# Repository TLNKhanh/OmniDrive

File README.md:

# OmniDrive

Dual H-bridge motor driver + ESP32 + USB-C PD, squeezed into a 45×59.5mm 2-layer board.

I wanted a board that could work with a single USB-C port and have it drive two motors (or 2 pairs if configured) while able to measure the board's current draw.

*Full schematic — click image or [open PDF](hardware/schematic.pdf)*

*PCB top copper layer — [open PDF](hardware/PCB_Top.pdf)*

*PCB bottom copper layer — [open PDF](hardware/PCB_Bottom.pdf)*

## What it does

- Drives 2 or 4 DC motors (configurable) with two DRV8833 H-bridges, one DRV8833 is optimal, up to 1.5A per channel.
- Negotiates power over USB-C via CH224K to get 9V from power supply
- Measures total motor current with an INA219 over I2C
- Lets you program the ESP32 over USB through the CH340C, with automatic boot/reset
- Breaks out power lines and 14 GPIOs + I2C on a header for sensors, encoders, whatever
- Configurable 2S / 1S battery pack via solder pads

## Why I built it

I wanted something that could serve for multiple RC car or stepper driving projects without having to combine separate modules.

## Specs

| Function| Component |
|------|------|
| MCU | ESP32-WROOM-32E |
| Motor drivers | 2× DRV8833 (HTSSOP-16 with thermal pad) |
| USB-C PD | CH224K sink, negotiates 9V |
| Current sense | INA219, 0.1Ω shunt, I2C |
| USB-UART | CH340C with auto DTR/RTS |
| Logic power | ME6211C50 (5V), ME6211C33 (3.3V) |
| Breakout | 12 GPIO through 2x 3x2 header, Power through 1x 3x1 header|
| PCB | 2-layer, 1.6mm FR4, 45×59.5mm |

## Power flow

USB-C VBUS → CH224K negotiates voltage → +BATT rail

+BATT splits three ways:
- Directly to the DRV8833 motor drivers
- Through a 5V LDO (ME6211C50) for the CH340C and other devices
- It also then goes through a 3.3V LDO (ME6211C33) for the ESP32, INA219, WS2812,...

Motor current goes through a shared 0.1Ω sense resistor before reaching the drivers, so the INA219 sees total bus current. Per-motor would need two INA219s (maybe for later).

## Known issues / things to fix

A few things I'll change next version:

- The ME6211C33 is rated for 500mA and ESP32 can spike past that during WiFi TX. On a long USB-C cable with some voltage drop, the battery rail might sag enough to make the 3.3V regulator drop out. An AP2112 or similar low-dropout part would be safer.

- Didn't add TVS diodes on the USB-C CC/D+/D- lines or the motor outputs

- As mentioned, only total motor current. Can't tell which motor is drawing what.

## Files in hardware/

```
hardware/
├── schematic.pdf          — full schematic (click to view)
├── PCB_Top.pdf            — top copper render
├── PCB_Bottom.pdf         — bottom copper render
├── gerbers.zip            — Gerbers + drill files
├── bom.csv                — BOM for JLCPCB assembly
├── pick-place.csv         — centroid file
├── kicad/                 — source KiCad project
└── photos/                — PNG renders of schematic + PCB
```

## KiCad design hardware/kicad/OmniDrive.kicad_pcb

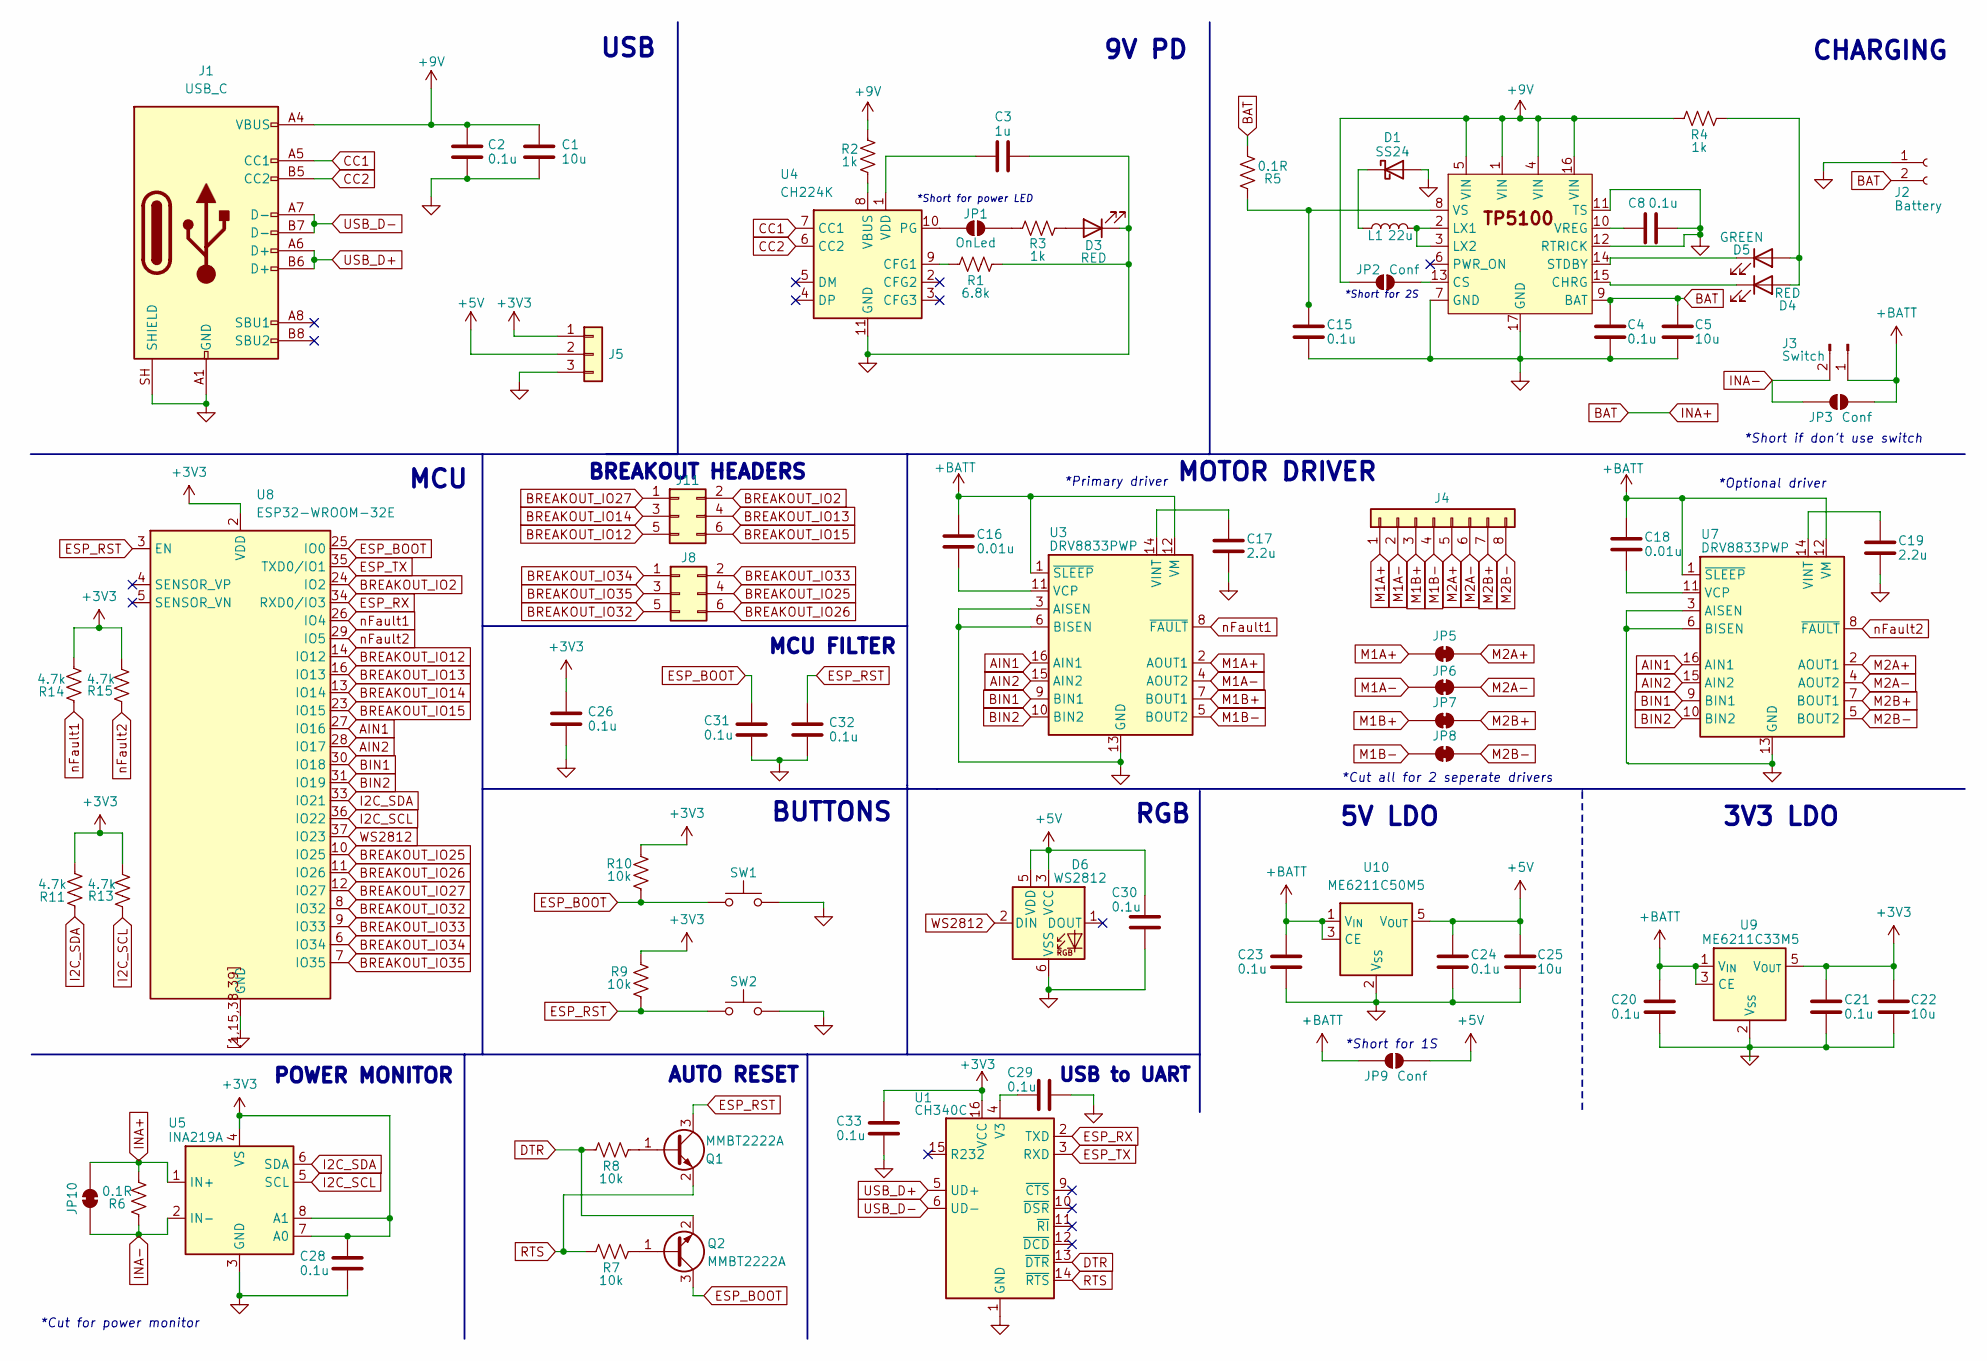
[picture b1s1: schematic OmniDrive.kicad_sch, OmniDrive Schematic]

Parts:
C1, C5, C22, C25: 10u; C_0603_1608Metric_Pad1.08x0.95mm_HandSolder
C2, C4, C8, C15, C20, C21, C23, C24, C26, C28, C29, C30, C31, C32, C33: 0.1u; C_0603_1608Metric_Pad1.08x0.95mm_HandSolder
C3: 1u; C_0603_1608Metric_Pad1.08x0.95mm_HandSolder
C16, C18: 0.01u; C_0603_1608Metric_Pad1.08x0.95mm_HandSolder
C17, C19: 2.2u; C_0603_1608Metric_Pad1.08x0.95mm_HandSolder
D1: SS24; D_SMA
D3, D4: RED; LED_0603_1608Metric_Pad1.05x0.95mm_HandSolder
D5: GREEN; LED_0603_1608Metric_Pad1.05x0.95mm_HandSolder
D6: WS2812; LED_WS2812_PLCC6_5.0x5.0mm_P1.6mm
J1: USB_C; USB_C_Receptacle_HCTL_HC-TYPE-C-16P-01A
J2: Battery; PinHeader_1x02_P2.54mm_Vertical
J3: Switch; PinHeader_1x02_P2.54mm_Vertical
J4: Conn_01x08; PinSocket_1x08_P2.54mm_Vertical
J5: Conn_01x03; PinSocket_1x03_P2.54mm_Vertical
J8, J11: Conn_02x03_Odd_Even; PinHeader_2x03_P2.54mm_Vertical
JP1: OnLed; SolderJumper-2_P1.3mm_Bridged_RoundedPad1.0x1.5mm
JP2, JP3, JP9: Conf; SolderJumper-2_P1.3mm_Open_TrianglePad1.0x1.5mm
JP5, JP6, JP7, JP8, JP10: BridgedJumper; SolderJumper-2_P1.3mm_Bridged_RoundedPad1.0x1.5mm
L1: 22u; L_Changjiang_FXL0630
Q1, Q2: MMBT2222A; SOT-23
R1: 6.8k; R_0603_1608Metric_Pad0.98x0.95mm_HandSolder
R2, R3, R4: 1k; R_0603_1608Metric_Pad0.98x0.95mm_HandSolder
R5, R6: 0.1R; R_2512_6332Metric_Pad1.40x3.35mm_HandSolder
R7, R8, R9, R10: 10k; R_0603_1608Metric_Pad0.98x0.95mm_HandSolder
R11, R13, R14, R15: 4.7k; R_0603_1608Metric_Pad0.98x0.95mm_HandSolder
SW1, SW2: SW_Push; SW_Push_1P1T_NO_E-Switch_TL3301NxxxxxG
U1: CH340C; SOIC-16_3.9x9.9mm_P1.27mm
U2: NXP_VQFN-16-1EP_4x4mm_P0.65mm_EP2.1x2.1mm
U3, U7: DRV8833PWP; HTSSOP-16-1EP_4.4x5mm_P0.65mm_EP3.4x5mm_Mask2.46x2.31mm_The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
U4: CH224K; SSOP-10-1EP_3.9x4.9mm_P1mm_EP2.1x3.3mm
U5: INA219A; SOT-23-8
U8: ESP32-WROOM-32E
U9: ME6211C33M5; SOT-23-5
U10: ME6211C50M5; SOT-23-5

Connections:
+3V3: C21.1, C22.1, C26.1, C28.1, C33.2, J5.1, R9.1, R10.1, R11.2, R13.2, R14.2, R15.2, U1.16 (VCC), U5.4 (VS), U5.7 (A0), U5.8 (A1), U8.2 (VDD), U9.5 (V_{OUT})
+5V: C24.1, C25.1, C30.1, D6.3 (VCC), D6.5 (VDD), J5.2, JP9.1 (A), U10.5 (V_{OUT})
+9V: C1.1, C2.1, J1.A4 (VBUS), J1.A9 (VBUS), J1.B4 (VBUS), J1.B9 (VBUS), JP2.2 (B), R2.2, R4.2, U2.1 (VIN), U2.4 (VIN), U2.5 (VIN), U2.16 (VIN)
+BATT: C16.1, C18.1, C20.1, C23.1, J3.1, JP3.1 (A), JP9.2 (B), U3.1 (~SLEEP), U3.12 (VM), U7.1 (~SLEEP), U7.12 (VM), U9.1 (V_{IN}), U9.3 (CE), U10.1 (V_{IN}), U10.3 (CE)
AIN1: U3.16 (AIN1), U7.16 (AIN1), U8.27 (IO16)
AIN2: U3.15 (AIN2), U7.15 (AIN2), U8.28 (IO17)
BAT: C4.1, C5.1, J2.2, JP10.2 (B), R5.1, R6.1, U2.9 (BAT), U5.1 (IN+)
BIN1: U3.9 (BIN1), U7.9 (BIN1), U8.30 (IO18)
BIN2: U3.10 (BIN2), U7.10 (BIN2), U8.31 (IO19)
BREAKOUT_IO2: J11.2, U8.24 (IO2)
BREAKOUT_IO12: J11.5, U8.14 (IO12)
BREAKOUT_IO13: J11.4, U8.16 (IO13)
BREAKOUT_IO14: J11.3, U8.13 (IO14)
BREAKOUT_IO15: J11.6, U8.23 (IO15)
BREAKOUT_IO25: J8.4, U8.10 (IO25)
BREAKOUT_IO26: J8.6, U8.11 (IO26)
BREAKOUT_IO27: J11.1, U8.12 (IO27)
BREAKOUT_IO32: J8.5, U8.8 (IO32)
BREAKOUT_IO33: J8.2, U8.9 (IO33)
BREAKOUT_IO34: J8.1, U8.6 (IO34)
BREAKOUT_IO35: J8.3, U8.7 (IO35)
CC1: J1.A5 (CC1), U4.7 (CC1)
CC2: J1.B5 (CC2), U4.6 (CC2)
DTR: Q2.2 (E), R8.2, U1.13 (~DTR)
ESP_BOOT: C31.1, Q2.3 (C), R10.2, SW1.1, U8.25 (IO0)
ESP_RST: C32.1, Q1.3 (C), R9.2, SW2.1, U8.3 (EN)
ESP_RX: U1.2 (TXD), U8.34 (RXD0/IO3)
ESP_TX: U1.3 (RXD), U8.35 (TXD0/IO1)
GND: C1.2, C2.2, C3.1, C4.2, C5.2, C8.2, C15.2, C17.2, C19.2, C20.2, C21.2, C22.2, C23.2, C24.2, C25.2, C26.2, C28.2, C29.1, C30.2, C31.2, C32.2, C33.1, D1.2 (A), D3.1 (K), D6.6 (VSS), J1.A1 (GND), J1.A12 (GND), J1.B1 (GND), J1.B12 (GND), J1.SH (SHIELD), J2.1, J5.3, R1.1, SW1.2, SW2.2, U1.1 (GND), U2.7 (GND), U2.11 (TS), U2.12 (RTRICK), U2.17 (GND), U3.3 (AISEN), U3.6 (BISEN), U3.13 (GND), U3.17 (GND), U4.11 (GND), U5.3 (GND), U7.3 (AISEN), U7.6 (BISEN), U7.13 (GND), U7.17 (GND), U8.1 (GND), U8.15 (GND), U8.38 (GND), U8.39 (GND), U8.[1,15,38,39] (GND), U9.2 (V_{SS}), U10.2 (V_{SS}); also elsewhere on the board
I2C_SCL: R13.1, U5.5 (SCL), U8.36 (IO22)
I2C_SDA: R11.1, U5.6 (SDA), U8.33 (IO21)
INA-: J3.2, JP3.2 (B), JP10.1 (A), R6.2, U5.2 (IN-)
M1A+: J4.1, JP5.1 (A), U3.2 (AOUT1)
M1A-: J4.2, JP6.1 (A), U3.4 (AOUT2)
M1B+: J4.3, JP7.1 (A), U3.7 (BOUT1)
M1B-: J4.4, JP8.1 (A), U3.5 (BOUT2)
M2A+: J4.5, JP5.2 (B), U7.2 (AOUT1)
M2A-: J4.6, JP6.2 (B), U7.4 (AOUT2)
M2B+: J4.7, JP7.2 (B), U7.7 (BOUT1)
M2B-: J4.8, JP8.2 (B), U7.5 (BOUT2)
unnamed 40: D1.1 (K), L1.1; also elsewhere on the board
unnamed: D3.2 (A), R3.1
unnamed: D4.2 (A), D5.2 (A), R4.1
unnamed: D4.1 (K), U2.15 (CHRG)
unnamed: D5.1 (K), U2.14 (STDBY)
unnamed: JP1.1 (A), R3.2
unnamed: JP1.2 (B), U4.10 (PG)
unnamed: JP2.1 (A), U2.13 (CS)
unnamed: Q1.1 (B), R8.1
unnamed: Q2.1 (B), R7.1
unnamed: C29.2, U1.4 (V3)
unnamed: L1.2, U2.2 (LX1), U2.3 (LX2)
unnamed: C8.1, U2.10 (VREG)
unnamed: C15.1, R5.2, U2.8 (VS)
unnamed: C16.2, U3.11 (VCP)
unnamed: C17.1, U3.14 (VINT)
unnamed: R1.2, U4.9 (CFG1)
unnamed: R2.1, U4.8 (VBUS)
unnamed: C3.2, U4.1 (VDD)
unnamed: C18.2, U7.11 (VCP)
unnamed: C19.1, U7.14 (VINT)
RTS: Q1.2 (E), R7.2, U1.14 (~RTS)
USB_D+: J1.A6 (D+), J1.B6 (D+), U1.5 (UD+)
USB_D-: J1.A7 (D-), J1.B7 (D-), U1.6 (UD-)
WS2812: D6.2 (DIN), U8.37 (IO23)
nFault1: R14.1, U3.8 (~FAULT), U8.26 (IO4)
nFault2: R15.1, U7.8 (~FAULT), U8.29 (IO5)

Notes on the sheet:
*Short for 1S
*Short for power LED
BREAKOUT HEADERS
*Short for 2S
3V3 LDO
POWER MONITOR
RGB
BUTTONS
*Primary driver
*Short if don't use switch
CHARGING
*Cut all for 2 seperate drivers
AUTO RESET
USB to UART
MCU
MOTOR DRIVER
5V LDO
USB
*Cut for power monitor
*Optional driver
9V PD
MCU FILTER

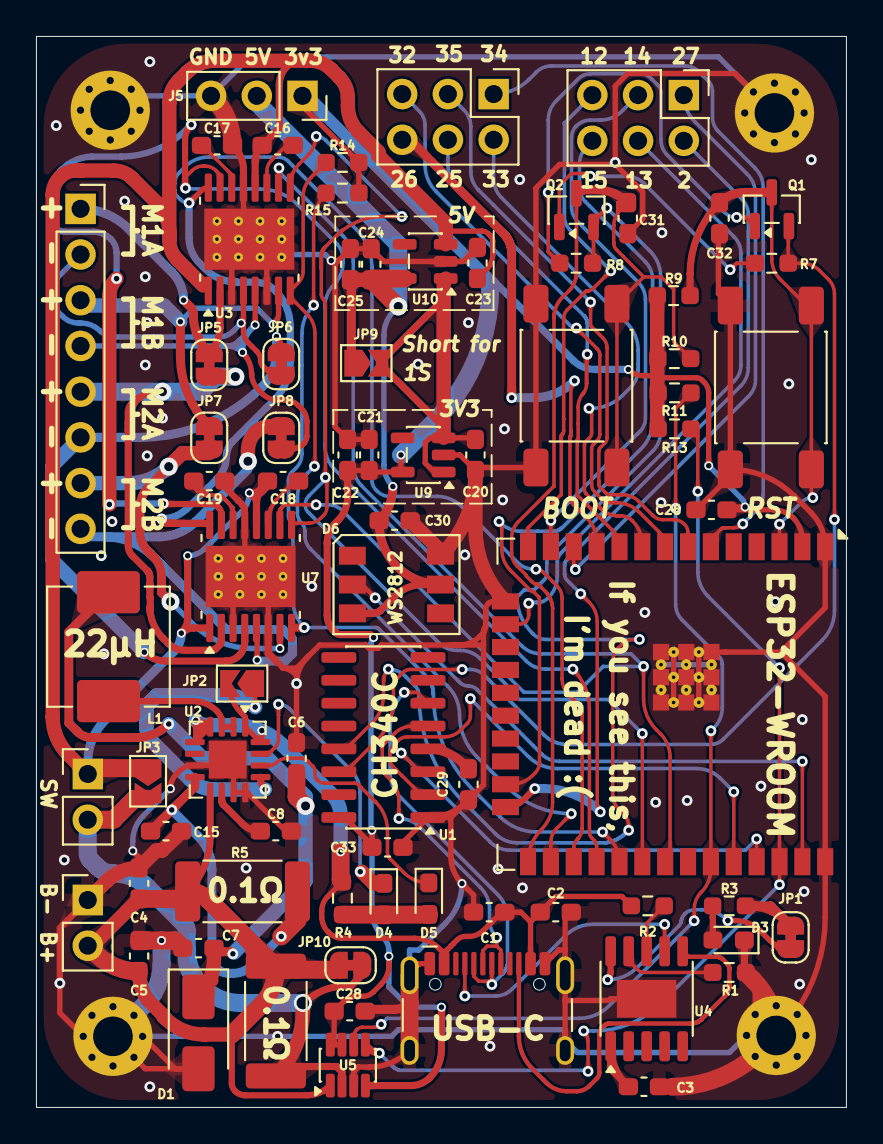
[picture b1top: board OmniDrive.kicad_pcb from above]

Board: 2 copper layers, 45.0 x 59.5 mm, 79 parts (0 on the bottom side), 67 nets.

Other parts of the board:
C6: 0.1u; C_0603_1608Metric_Pad1.08x0.95mm_HandSolder
C7: 10u; C_0603_1608Metric_Pad1.08x0.95mm_HandSolder
HoleA: MountingHole_2.2mm_M2_Pad_Via
HoleB: MountingHole_2.2mm_M2_Pad_Via
HoleC: MountingHole_2.2mm_M2_Pad_Via
HoleD: MountingHole_2.2mm_M2_Pad_Via

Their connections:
GND: C6.2, C7.2, HoleA.1, HoleB.1, HoleC.1, HoleD.1; also elsewhere on the board
unnamed 40: C6.1, C7.1; also elsewhere on the board

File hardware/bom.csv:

"Reference","Value","Footprint","LCSC Part #","DNP"
"C1,C5,C22,C25","10u","Capacitor_SMD:C_0603_1608Metric_Pad1.08x0.95mm_HandSolder","",""
"C2,C4,C8,C15,C20,C21,C23,C24,C26,C28-C33","0.1u","Capacitor_SMD:C_0603_1608Metric_Pad1.08x0.95mm_HandSolder","",""
"C3","1u","Capacitor_SMD:C_0603_1608Metric_Pad1.08x0.95mm_HandSolder","",""
"C16,C18","0.01u","Capacitor_SMD:C_0603_1608Metric_Pad1.08x0.95mm_HandSolder","",""
"C17,C19","2.2u","Capacitor_SMD:C_0603_1608Metric_Pad1.08x0.95mm_HandSolder","",""
"D1","SS24","Diode_SMD:D_SMA","",""
"D3,D4","RED","LED_SMD:LED_0603_1608Metric_Pad1.05x0.95mm_HandSolder","",""
"D5","GREEN","LED_SMD:LED_0603_1608Metric_Pad1.05x0.95mm_HandSolder","",""
"D6","WS2812","LED_SMD:LED_WS2812_PLCC6_5.0x5.0mm_P1.6mm","",""
"J1","USB_C","Connector_USB:USB_C_Receptacle_HCTL_HC-TYPE-C-16P-01A","",""
"J2","Battery","Connector_PinHeader_2.54mm:PinHeader_1x02_P2.54mm_Vertical","",""
"J3","Switch","Connector_PinHeader_2.54mm:PinHeader_1x02_P2.54mm_Vertical","",""
"J4","Conn_01x08","Connector_PinSocket_2.54mm:PinSocket_1x08_P2.54mm_Vertical","",""
"J5","Conn_01x03","Connector_PinSocket_2.54mm:PinSocket_1x03_P2.54mm_Vertical","",""
"J8,J11","Conn_02x03_Odd_Even","Connector_PinHeader_2.54mm:PinHeader_2x03_P2.54mm_Vertical","",""
"L1","22u","Inductor_SMD:L_Changjiang_FXL0630","",""
"Q1,Q2","MMBT2222A","Package_TO_SOT_SMD:SOT-23","",""
"R1","6.8k","Resistor_SMD:R_0603_1608Metric_Pad0.98x0.95mm_HandSolder","",""
"R2-R4","1k","Resistor_SMD:R_0603_1608Metric_Pad0.98x0.95mm_HandSolder","",""
"R5,R6","0.1R","Resistor_SMD:R_2512_6332Metric_Pad1.40x3.35mm_HandSolder","",""
"R7-R10","10k","Resistor_SMD:R_0603_1608Metric_Pad0.98x0.95mm_HandSolder","",""
"R11,R13-R15","4.7k","Resistor_SMD:R_0603_1608Metric_Pad0.98x0.95mm_HandSolder","",""
"SW1,SW2","SW_Push","Button_Switch_SMD:SW_Push_1P1T_NO_E-Switch_TL3301NxxxxxG","",""
"U1","CH340C","Package_SO:SOIC-16_3.9x9.9mm_P1.27mm","",""
"U2","","Package_DFN_QFN:NXP_VQFN-16-1EP_4x4mm_P0.65mm_EP2.1x2.1mm","",""
"U3,U7","DRV8833PWP","Package_SO:HTSSOP-16-1EP_4.4x5mm_P0.65mm_EP3.4x5mm_Mask2.46x2.31mm_ThermalVias","",""
"U4","CH224K","Package_SO:SSOP-10-1EP_3.9x4.9mm_P1mm_EP2.1x3.3mm","",""
"U5","INA219A","Package_TO_SOT_SMD:SOT-23-8","",""
"U8","ESP32-WROOM-32E","RF_Module:ESP32-WROOM-32E","",""
"U9","ME6211C33M5","Package_TO_SOT_SMD:SOT-23-5","",""
"U10","ME6211C50M5","Package_TO_SOT_SMD:SOT-23-5","",""
